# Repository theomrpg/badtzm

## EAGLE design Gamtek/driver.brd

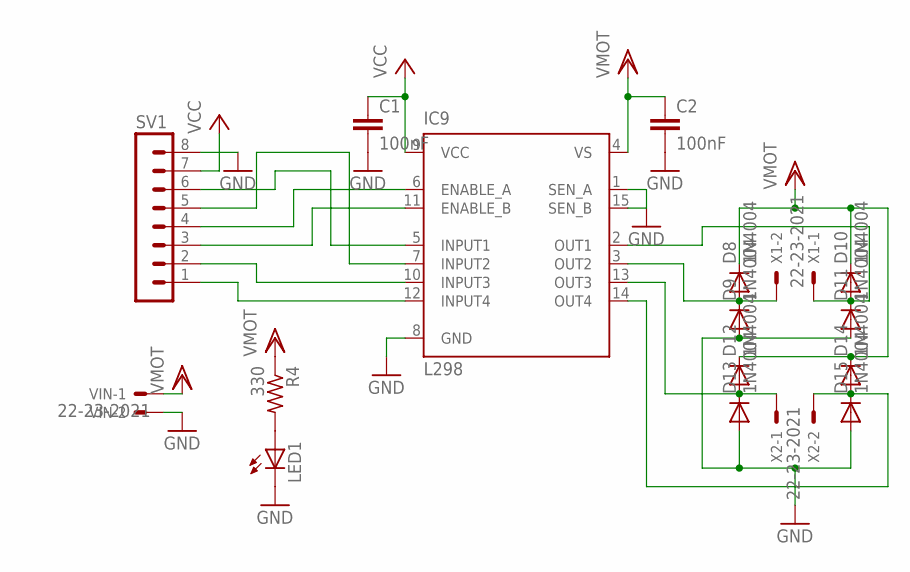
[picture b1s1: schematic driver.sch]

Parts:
C1, C2: 100nF; C025-025X050
D8, D9, D10, D11, D12, D13, D14, D15: 1N4004; DO41-10
IC9: L298; MULTIWATT-15
LED1: LED3MM
R4: 330; 0207/10
SV1: MA08-1
VIN: 22-23-2021; MPN 22-23-2021
X1, X2: 22-23-2021

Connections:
GND: C1.2, C2.2, D9.A, D11.A, D13.A, D15.A, IC9.1 (SEN_A), IC9.8 (GND), IC9.15 (SEN_B), LED1.K (C), SV1.8, VIN.2
unnamed: IC9.5 (INPUT1), SV1.6
unnamed: IC9.7 (INPUT2), SV1.5
unnamed: IC9.12 (INPUT4), SV1.1
unnamed: IC9.10 (INPUT3), SV1.2
unnamed: IC9.6 (ENABLE_A), SV1.4
unnamed: IC9.11 (ENABLE_B), SV1.3
unnamed: LED1.A, R4.2
unnamed: D8.A, D9.C, IC9.3 (OUT2), X1.2
unnamed: D10.A, D11.C, IC9.2 (OUT1), X1.1
unnamed: D12.A, D13.C, IC9.13 (OUT3), X2.1
unnamed: D14.A, D15.C, IC9.14 (OUT4), X2.2
VCC: C1.1, IC9.9 (VCC), SV1.7
VDD: C2.1, D8.C, D10.C, D12.C, D14.C, IC9.4 (VS), R4.1, VIN.1

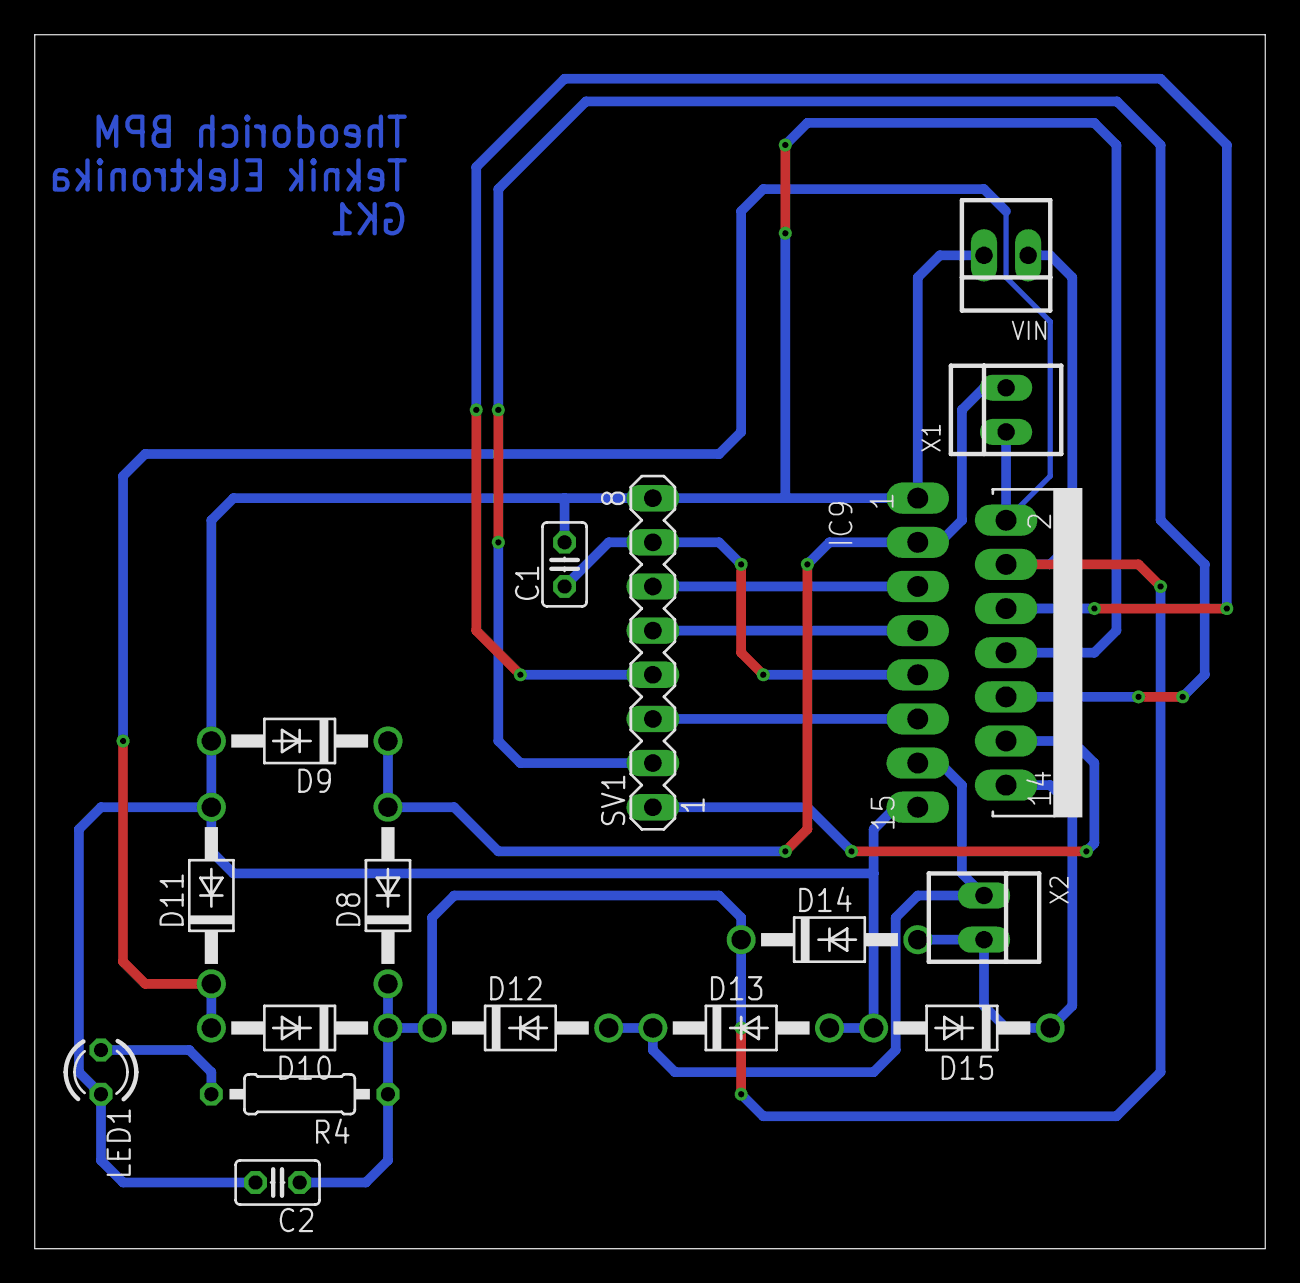
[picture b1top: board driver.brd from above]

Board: 2 copper layers, 70.8 x 69.8 mm, 17 parts (0 on the bottom side), 14 nets.

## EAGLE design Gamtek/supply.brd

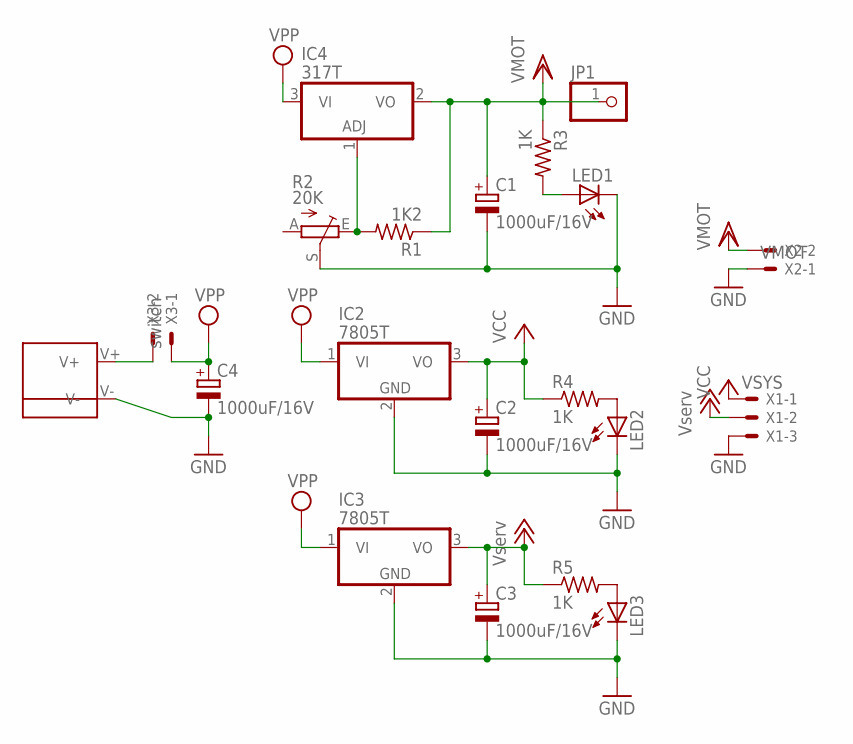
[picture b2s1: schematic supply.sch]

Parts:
C1, C2, C3, C4: 1000uF/16V; E3,5-10
IC2, IC3: 7805T; TO220H
IC4: 317T; TO220H
JP1: PINHD-1X1; 1X01
LED1, LED2, LED3: LED3MM
R1: 1K2; 0207/10
R2: 20K; CA6V
R3, R4, R5: 1K; 0207/10
VIN: CON-XT60M
X1: VSYS; 22-23-2031
X2: VMOT; 22-23-2021
X3: switch; 22-23-2021; MPN 22-23-2021

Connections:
+12V: C3.+, IC3.3 (VO), R5.1, X1.2
GND: C1.-, C2.-, C3.-, C4.-, IC2.2 (GND), IC3.2 (GND), LED1.K (C), LED2.K (C), LED3.K (C), R2.S, VIN.V-, X1.3, X2.1
unnamed: IC4.1 (ADJ), R1.2, R2.E
unnamed: LED1.A, R3.2
unnamed: LED3.A, R5.2
unnamed: VIN.V+, X3.2
unnamed: LED2.A, R4.2
VCC: C2.+, IC2.3 (VO), R4.1, X1.1
VDD: C1.+, IC4.2 (VO), JP1.1, R1.1, R3.1, X2.2
VPP: C4.+, IC2.1 (VI), IC3.1 (VI), IC4.3 (VI), X3.1

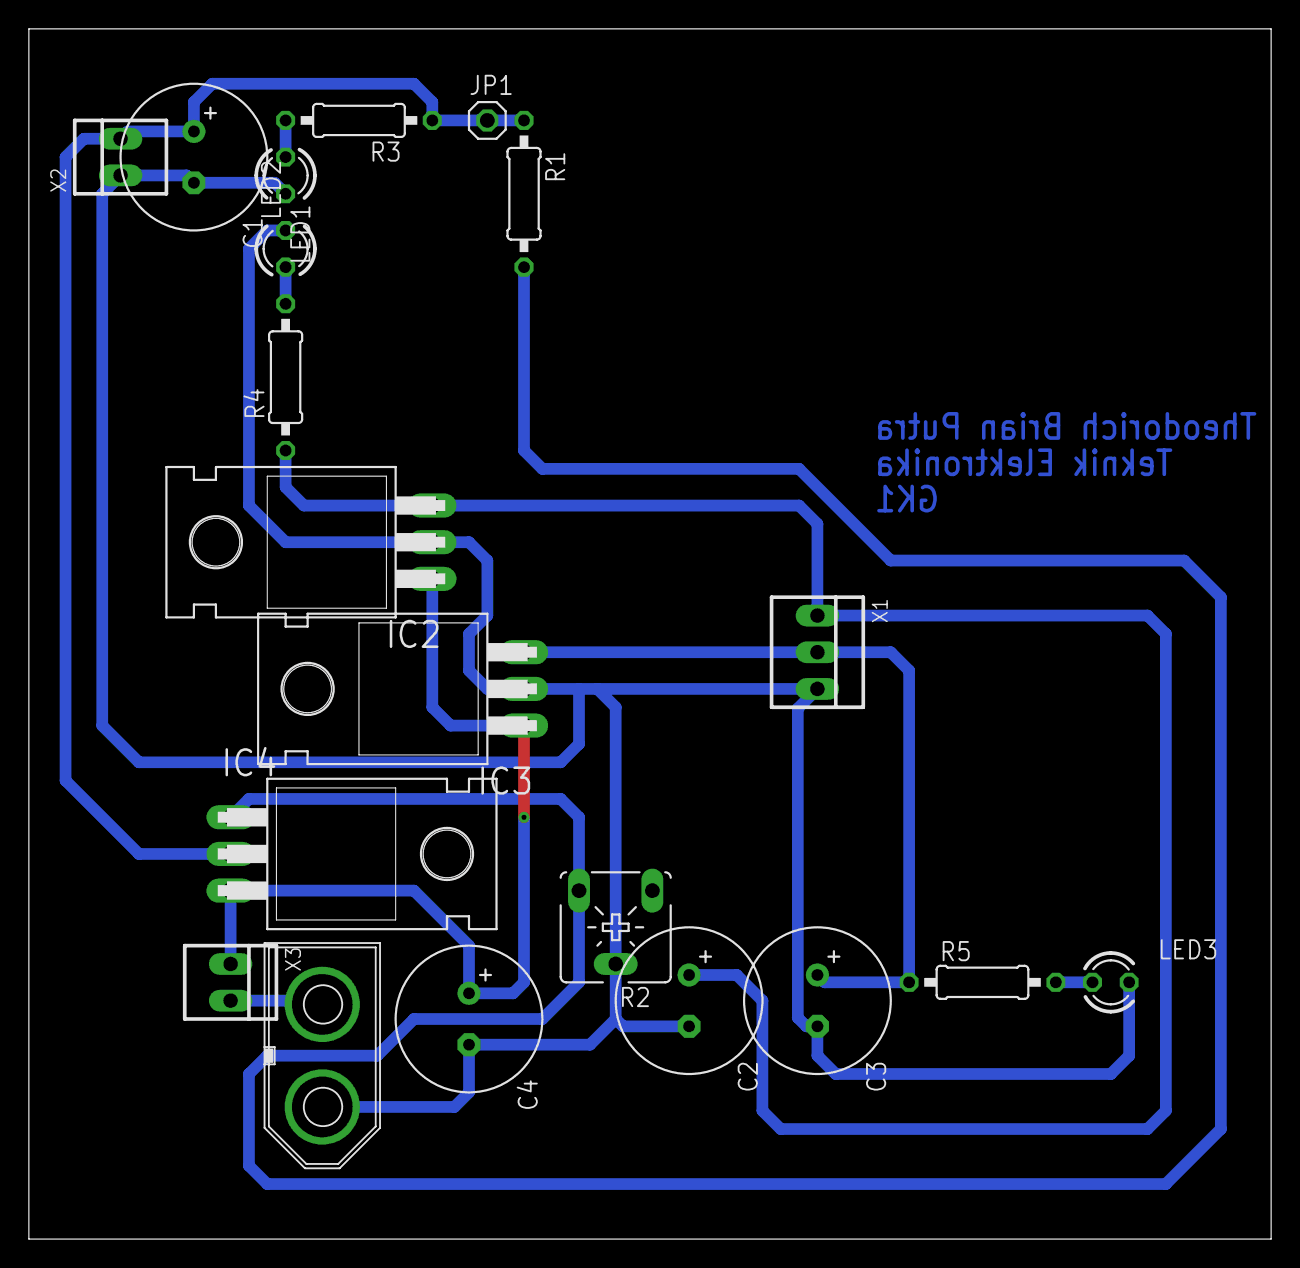
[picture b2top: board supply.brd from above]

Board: 2 copper layers, 86.0 x 83.8 mm, 20 parts (0 on the bottom side), 10 nets.

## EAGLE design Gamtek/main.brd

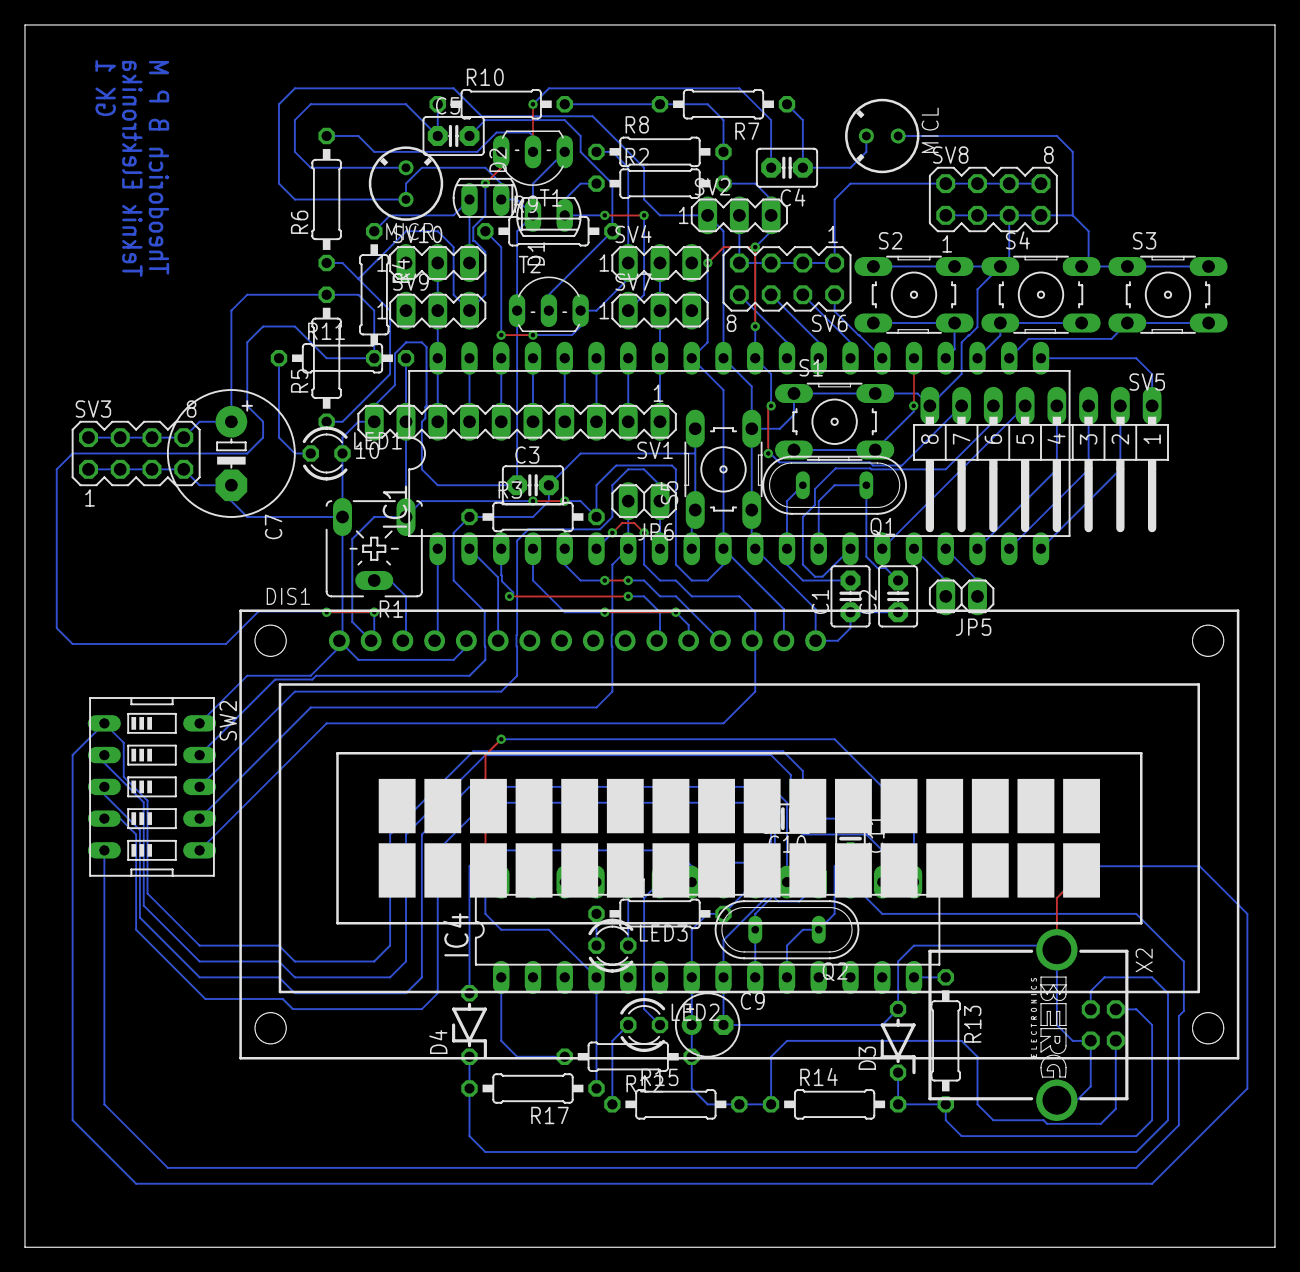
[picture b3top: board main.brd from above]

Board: 2 copper layers, 100.0 x 97.8 mm, 61 parts (0 on the bottom side), 65 nets.

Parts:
C1, C2: 22p; C2.5-3
C3: 10nF; C2.5-3
C4, C5: 100nF; C2.5-3
C7: 1000uF/16V; E5-10,5
C9: 10uF/16V; E2,5-5
C10, C11: 22pF; C025-024X044
D1, D2: SFH225
D3, D4: DZ3,6V; ZDIO-5
DIS1: TUXGR_16X2_R2
IC1: MEGA16-P; DIL40
IC4: MEGA8-P; DIL28-3
JP5, JP6: 1X02
LED1: merah; LED3MM
LED2: Merah; LED3MM
LED3: hijau; LED3MM
MICL: MC; F6050AP
MICR: MC; F6050AP
Q1: 8MHz; QS
Q2: 12MHz; QS
R1: 20K; CA6V
R2, R4: 56K; 0207/10
R3, R5, R7, R8, R10, R12: 10K; 0207/10
R6, R9: 100K; 0207/10
R11, R15, R16: 330; 0207/10
R13, R17: 68; 0207/10
R14: 2K2; 0207/10
S1, S2, S3, S4, S5: B3F-10XX
SV1: MA10-1
SV2, SV4, SV7, SV9, SV10: MA03-1
SV3, SV6, SV8: MA04-2
SV5: MA08-1W
SW2: EDG-05
T1, T2: TO92-EBC
X2: PN61729-S

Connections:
DGND: C9.-, C10.1, C11.1, D3.A, D4.A, IC4.8, IC4.22, SW2.1, X2.4, X2.S1, X2.S2
GND: C1.1, C2.1, C3.1, C7.-, D1.K, D2.K, DIS1.1, DIS1.5, DIS1.16, IC1.11, IC1.31, LED1.K, MICL.1, MICR.1, R1.E, S1.1, S1.2, S2.1, S2.2, S3.1, S3.2, S4.1, S4.2, S5.3, S5.4, SV1.10, SV2.1, SV3.1, SV3.3, SV3.5, SV3.7, SV5.8, SV8.1, SV8.3, SV8.5, SV8.7, SW2.10, T1.E, T2.E
MISO: IC1.7, JP6.2, SW2.7
MOSI: DIS1.14, IC1.6, SW2.6
unnamed: IC1.33, SV1.1, SV4.2, SV7.2
unnamed: IC1.34, SV1.2
unnamed: IC1.35, SV1.3
unnamed: IC1.36, SV1.4
unnamed: IC1.37, SV1.5
unnamed: IC1.38, SV1.6
unnamed: IC1.39, SV1.7
unnamed: D2.A, R4.1, SV10.3
unnamed: IC1.24, S2.3, S2.4
unnamed: DIS1.13, IC1.5
unnamed: DIS1.12, IC1.4
unnamed: DIS1.11, IC1.3
unnamed: DIS1.6, IC1.2
unnamed: R5.1, R6.1, SV9.3, T1.C
unnamed: DIS1.3, R1.S
unnamed: C1.2, IC1.12, Q1.2
unnamed: C2.2, IC1.13, Q1.1
unnamed: DIS1.4, IC1.1
unnamed: D1.A, R2.1, SV7.1
unnamed: IC1.23, S4.3, S4.4
unnamed: IC1.40, SV1.8, SV9.2, SV10.2
unnamed: C4.2, R6.2, T1.B
unnamed: C4.1, MICL.2, R7.1
unnamed: R8.1, R9.1, SV4.1, T2.C
unnamed: C5.2, R9.2, T2.B
unnamed: C5.1, MICR.2, R10.1
unnamed: IC1.22, S3.3, S3.4
unnamed: IC1.25, S1.3, S1.4
unnamed: IC1.21, SV5.1
unnamed: IC1.20, SV5.2
unnamed: IC1.19, SV5.3
unnamed: IC1.18, SV5.4
unnamed: IC1.15, SV5.5
unnamed: IC1.14, SV5.6
unnamed: IC1.16, JP5.2
unnamed: IC1.17, JP5.1
unnamed: LED1.A, R11.1
unnamed: IC4.1, R12.2
unnamed: IC1.26, SV6.2
unnamed: IC1.27, SV6.4
unnamed: IC1.28, SV6.6
unnamed: IC1.29, SV6.8
unnamed: C10.2, IC4.9, Q2.2
unnamed: C11.2, IC4.10, Q2.1
unnamed: IC4.14, R13.1
unnamed: LED2.A, R15.1
unnamed: LED3.A, R16.1
unnamed: IC4.23, LED2.K
unnamed: IC4.24, LED3.K
unnamed: D4.C, R17.2, X2.3
unnamed: IC4.4, IC4.15, R17.1
unnamed: D3.C, R13.2, R14.2, X2.2
unnamed: IC4.17, SW2.5
unnamed: IC4.18, SW2.4
unnamed: IC4.19, SW2.3
unnamed: IC4.16, SW2.2
RESET: C3.2, IC1.9, R3.1, S5.1, S5.2, SW2.9
SCK: IC1.8, JP6.1, SW2.8
VCC: C7.+, DIS1.2, DIS1.15, IC1.10, IC1.30, IC1.32, R1.A, R2.2, R3.2, R4.2, R5.2, R7.2, R8.2, R10.2, R11.2, SV1.9, SV2.3, SV3.2, SV3.4, SV3.6, SV3.8, SV5.7
VDD: SV2.2, SV6.1, SV6.3, SV6.5, SV6.7, SV8.2, SV8.4, SV8.6, SV8.8
VPP: C9.+, IC4.7, IC4.20, R12.1, R14.1, R15.2, R16.2, X2.1

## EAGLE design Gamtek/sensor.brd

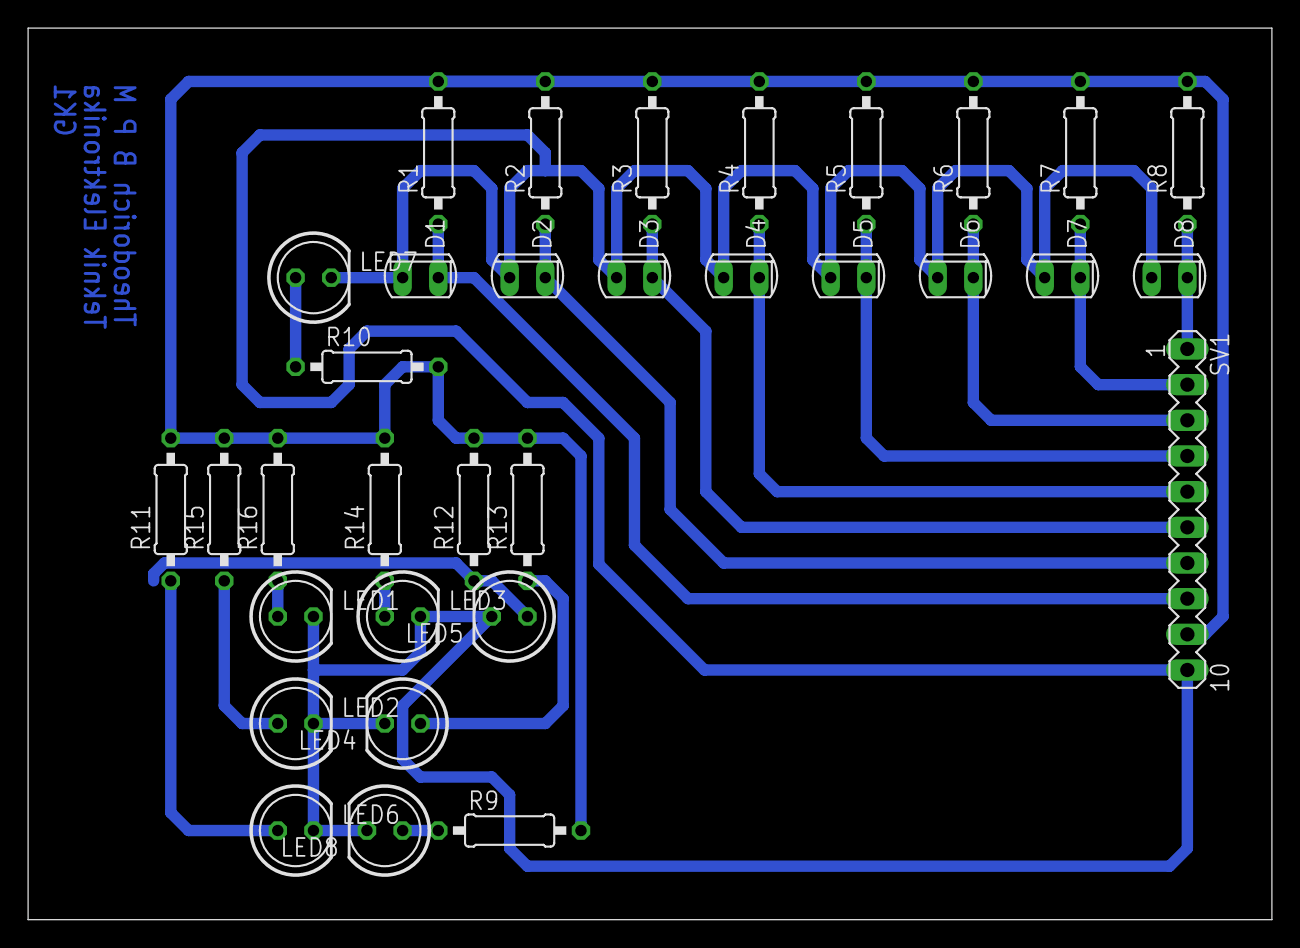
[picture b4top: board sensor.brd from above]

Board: 2 copper layers, 88.6 x 63.5 mm, 33 parts (0 on the bottom side), 18 nets.

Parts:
D1, D2, D3, D4, D5, D6, D7, D8: PhotoDioda; SFH225
LED1, LED2, LED3, LED4, LED5, LED6, LED7, LED8: LED putih SB; LED5MM
R1, R2, R3, R4, R5, R6, R7, R8: 0207/10
R9, R10, R11, R12, R13, R14, R15, R16: 330; 0207/10
SV1: MA10-1

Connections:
GND: D1.A, D2.A, D3.A, D4.A, D5.A, D6.A, D7.A, D8.A, LED1.K, LED2.K, LED3.K, LED4.K, LED5.K, LED6.K, LED7.K, LED8.K, SV1.10
unnamed: LED7.A, R10.1
unnamed: D7.K, R7.1, SV1.2
unnamed: D8.K, R8.1, SV1.1
unnamed: D1.K, R1.1, SV1.8
unnamed: D2.K, R2.1, SV1.7
unnamed: D3.K, R3.1, SV1.6
unnamed: D5.K, R5.1, SV1.4
unnamed: D4.K, R4.1, SV1.5
unnamed: D6.K, R6.1, SV1.3
unnamed: LED6.A, R11.1
unnamed: LED5.A, R12.1
unnamed: LED4.A, R13.1
unnamed: LED3.A, R14.1
unnamed: LED2.A, R15.1
unnamed: LED1.A, R16.1
unnamed: LED8.A, R9.1
VCC: R1.2, R2.2, R3.2, R4.2, R5.2, R6.2, R7.2, R8.2, R9.2, R10.2, R11.2, R12.2, R13.2, R14.2, R15.2, R16.2, SV1.9
